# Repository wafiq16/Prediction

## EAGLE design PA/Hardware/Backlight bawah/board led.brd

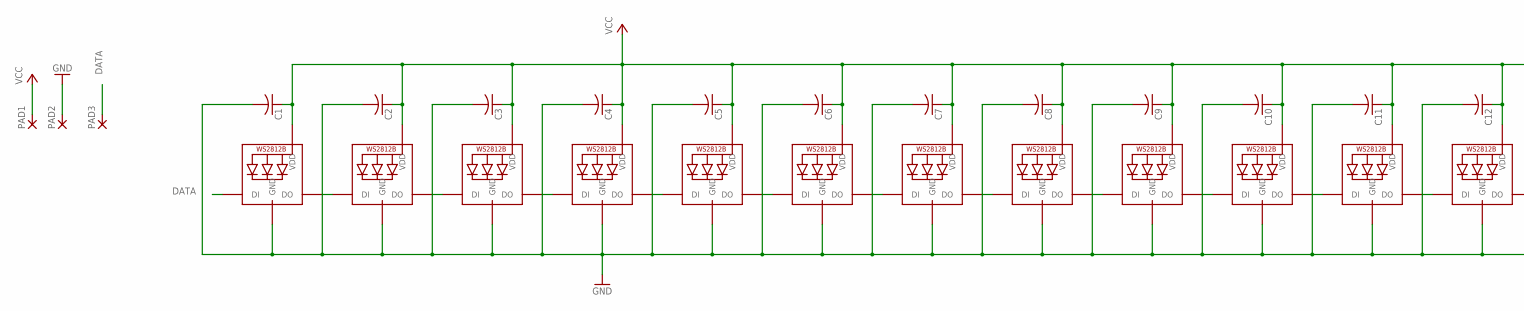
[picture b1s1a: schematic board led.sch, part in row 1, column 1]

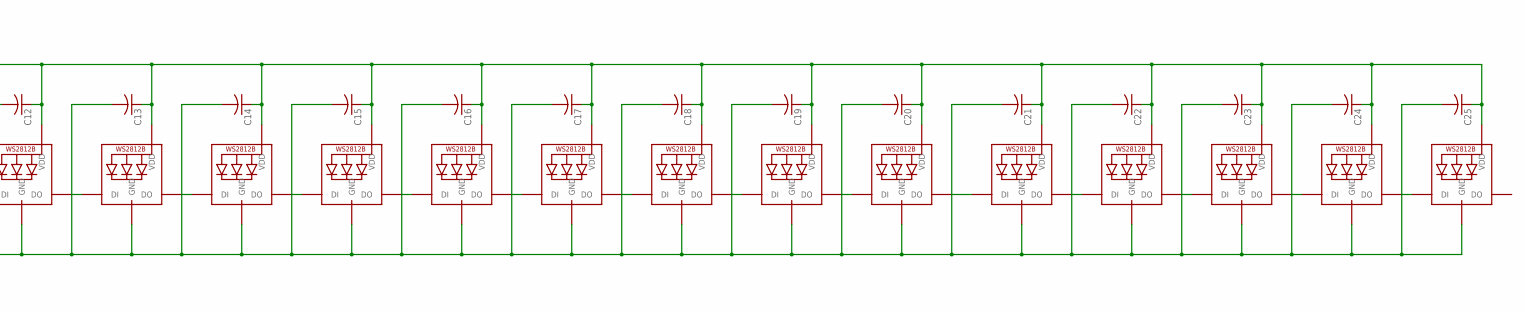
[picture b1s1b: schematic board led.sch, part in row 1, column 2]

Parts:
C1, C2, C3, C4, C5, C6, C7, C8, C9, C10, C11, C12, C13, C14, C15, C16, C17, C18, C19, C20, C21, C22, C23, C24, C25: C-USC0805; C0805
LED1, LED2, LED3, LED4, LED5, LED6, LED7, LED8, LED9, LED10, LED11, LED12, LED13, LED14, LED15, LED16, LED17, LED18, LED19, LED20, LED21, LED22, LED23, LED24, LED25: WS2812B5050; WS2812B
PAD1, PAD2, PAD3: SMD5; SMD2,54-5,08

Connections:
DATA: LED1.4-DIN (DI), PAD3.1
GND: C1.2, C2.2, C3.2, C4.2, C5.2, C6.2, C7.2, C8.2, C9.2, C10.2, C11.2, C12.2, C13.2, C14.2, C15.2, C16.2, C17.2, C18.2, C19.2, C20.2, C21.2, C22.2, C23.2, C24.2, C25.2, LED1.3-GND (GND), LED2.3-GND (GND), LED3.3-GND (GND), LED4.3-GND (GND), LED5.3-GND (GND), LED6.3-GND (GND), LED7.3-GND (GND), LED8.3-GND (GND), LED9.3-GND (GND), LED10.3-GND (GND), LED11.3-GND (GND), LED12.3-GND (GND), LED13.3-GND (GND), LED14.3-GND (GND), LED15.3-GND (GND), LED16.3-GND (GND), LED17.3-GND (GND), LED18.3-GND (GND), LED19.3-GND (GND), LED20.3-GND (GND), LED21.3-GND (GND), LED22.3-GND (GND), LED23.3-GND (GND), LED24.3-GND (GND), LED25.3-GND (GND), PAD2.1
unnamed: LED1.2-DOUT (DO), LED2.4-DIN (DI)
unnamed: LED2.2-DOUT (DO), LED3.4-DIN (DI)
unnamed: LED3.2-DOUT (DO), LED4.4-DIN (DI)
unnamed: LED4.2-DOUT (DO), LED5.4-DIN (DI)
unnamed: LED5.2-DOUT (DO), LED6.4-DIN (DI)
unnamed: LED6.2-DOUT (DO), LED7.4-DIN (DI)
unnamed: LED7.2-DOUT (DO), LED8.4-DIN (DI)
unnamed: LED8.2-DOUT (DO), LED9.4-DIN (DI)
unnamed: LED9.2-DOUT (DO), LED10.4-DIN (DI)
unnamed: LED10.2-DOUT (DO), LED11.4-DIN (DI)
unnamed: LED11.2-DOUT (DO), LED12.4-DIN (DI)
unnamed: LED12.2-DOUT (DO), LED13.4-DIN (DI)
unnamed: LED13.2-DOUT (DO), LED14.4-DIN (DI)
unnamed: LED14.2-DOUT (DO), LED15.4-DIN (DI)
unnamed: LED15.2-DOUT (DO), LED16.4-DIN (DI)
unnamed: LED16.2-DOUT (DO), LED17.4-DIN (DI)
unnamed: LED17.2-DOUT (DO), LED18.4-DIN (DI)
unnamed: LED18.2-DOUT (DO), LED19.4-DIN (DI)
unnamed: LED19.2-DOUT (DO), LED20.4-DIN (DI)
unnamed: LED21.2-DOUT (DO), LED22.4-DIN (DI)
unnamed: LED22.2-DOUT (DO), LED23.4-DIN (DI)
unnamed: LED23.2-DOUT (DO), LED24.4-DIN (DI)
unnamed: LED24.2-DOUT (DO), LED25.4-DIN (DI)
unnamed: LED20.2-DOUT (DO), LED21.4-DIN (DI)
VCC: C1.1, C2.1, C3.1, C4.1, C5.1, C6.1, C7.1, C8.1, C9.1, C10.1, C11.1, C12.1, C13.1, C14.1, C15.1, C16.1, C17.1, C18.1, C19.1, C20.1, C21.1, C22.1, C23.1, C24.1, C25.1, LED1.1-VDD (VDD), LED2.1-VDD (VDD), LED3.1-VDD (VDD), LED4.1-VDD (VDD), LED5.1-VDD (VDD), LED6.1-VDD (VDD), LED7.1-VDD (VDD), LED8.1-VDD (VDD), LED9.1-VDD (VDD), LED10.1-VDD (VDD), LED11.1-VDD (VDD), LED12.1-VDD (VDD), LED13.1-VDD (VDD), LED14.1-VDD (VDD), LED15.1-VDD (VDD), LED16.1-VDD (VDD), LED17.1-VDD (VDD), LED18.1-VDD (VDD), LED19.1-VDD (VDD), LED20.1-VDD (VDD), LED21.1-VDD (VDD), LED22.1-VDD (VDD), LED23.1-VDD (VDD), LED24.1-VDD (VDD), LED25.1-VDD (VDD), PAD1.1

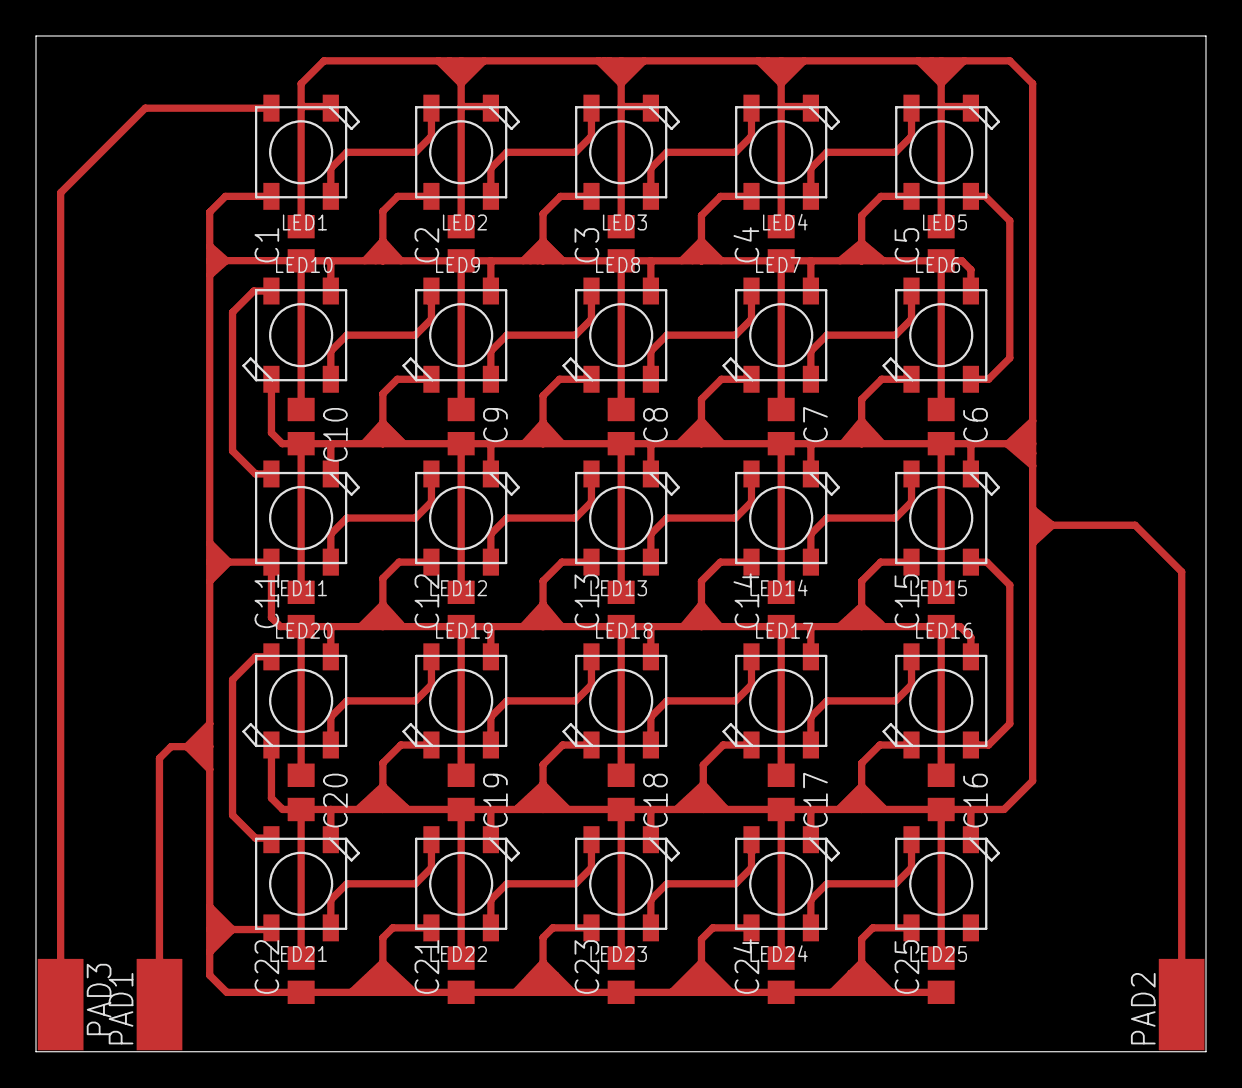
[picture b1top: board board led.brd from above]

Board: 2 copper layers, 65.0 x 56.4 mm, 53 parts (0 on the bottom side), 27 nets.

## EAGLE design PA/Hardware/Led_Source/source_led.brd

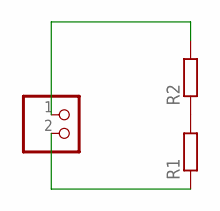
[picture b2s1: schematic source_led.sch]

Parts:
JP1: PINHD-1X2; 1X02
R1, R2: R-EU_0204/7; 0204/7

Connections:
unnamed: JP1.2, R1.1
unnamed: JP1.1, R2.2
unnamed: R1.2, R2.1

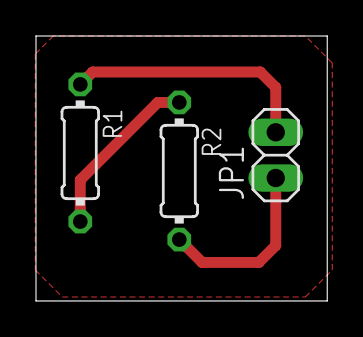
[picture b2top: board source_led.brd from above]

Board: 2 copper layers, 16.2 x 14.7 mm, 3 parts (0 on the bottom side), 3 nets.

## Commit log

2021-08-14 neural network data set
2021-08-14 generate dummy data for test training code
2021-08-14 model for regression
2021-08-14 python backpropagation methode
2021-08-14 tensorflow multiclass classification training code
2021-08-14 tensorflow regression prediction training
2021-09-24 add newest update
2022-03-13 add newest update including design, code and etc
2022-04-07 update progress
